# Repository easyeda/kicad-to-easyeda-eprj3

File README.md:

English | [中文](README.zh-CN.md)

# kicad-to-easyeda-eprj3

Convert KiCAD project files to the eprj3 project format of EasyEDA Pro, and KiCad libraries to the EasyEDA Pro library format `.elibz2`.

## Features

- **Project conversion**: Batch-traverses all `.kicad_sch` / `.kicad_pcb` files under a directory and generates a complete eprj3 folder project (`<name>.eprj3` index + `sch/` + `pcb/`)
- **Library conversion**: Packs all KiCad libraries under a directory (`*.kicad_sym` symbol libs + `*.pretty/*.kicad_mod` footprint libs) into a single EasyEDA Pro library file `.elibz2`
- **No-install browser version**: `kicad-to-eprj3.html` converts projects entirely in the browser (no Node.js, no upload)
- **Standalone JS**: one file usable both as a Node.js CLI and as a browser script, built by `npm run build`

## Requirements

- Node.js ≥ 18. There are **no npm dependencies** (runtime or development); the browser page needs none either.

## Browser version (no installation)

Download `kicad-to-eprj3-<version>.zip` from the GitHub **Releases** page and unzip it. Open `kicad-to-eprj3.html` in a recent Chrome/Edge:

1. Add one or more KiCad project folders. Clicking a folder scans it and lists the projects inside, so several can be ticked at once; multiple folders can also be dropped together, and the picker can be used repeatedly.
2. Click **Convert** — everything is processed locally; nothing is uploaded.
3. Download the `.eprj3.zip`, unzip it, then open `<project>/<project>.eprj3` in EasyEDA Pro.

Choosing a folder uses the browser's File System Access API, so no “upload files” confirmation appears (Chrome/Edge).

The zip also contains the standalone JS, this guide (bilingual) and the license.

### Online (GitHub Pages)

The page is also published as a single-page site: **https://easyeda.github.io/kicad-to-easyeda-eprj3/**

`.github/workflows/pages.yml` builds `dist/kicad-to-eprj3.html` and deploys it as the Pages `index.html` on every push to `main` (or manually via *Actions → Deploy browser page to GitHub Pages → Run workflow*). In a fork, enable **Settings → Pages → Build and deployment → Source: GitHub Actions** once; the workflow can also try to enable it on the first run.

> If your organization disables GitHub Pages for the repository, the workflow detects it and skips deployment with a notice (no red build). The same single file is also attached to every GitHub Release — download **`kicad-to-eprj3.html`** and open it locally, or host it on any static file server. No build step is needed to use it.

## Usage

### 1) KiCad project → eprj3 project (batch)

```bash
node scripts/convert-kicad.js convert <KiCad project directory> <output directory> [--project-name <name>]
```

Example — convert the sample project shipped with this repository:

```bash
node scripts/convert-kicad.js convert example/kicad/kicad-project ./eprj3 --project-name kicad-project
```

Output:

```text
Created eprj3 project at D:/…/eprj3
  sch: kicad-project.kicad_sch -> D:/…/eprj3/sch/Schematic1/P1.esch2
  pcb: kicad-project.kicad_pcb -> D:/…/eprj3/pcb/PCB1.epcb2
```

The generated project (`<output directory>/kicad-project.eprj3`, containing `sch/` and `pcb/`) can be opened directly in EasyEDA Pro.

- The two directories are passed positionally: 1st is the KiCad project directory, 2nd is the eprj3 output directory
- Each `*.kicad_sch` under the source directory generates one schematic (`Schematic1`, `Schematic2`, …), and each `*.kicad_pcb` generates one board (`PCB1`, `PCB2`, …)

### 2) KiCad library directory → EasyEDA Pro library package (.elibz2)

```bash
node scripts/convert-kicad-lib.js convert <KiCad library directory> <output.elibz2> [--name <LibName>]
```

Example — put symbol and footprint libraries into one directory and pack them together (the scan is non-recursive; `.kicad_sym` files and `.pretty/` directories must be direct children):

```text
mylibs/
├── Device.kicad_sym
├── LED.kicad_sym
├── Resistor_SMD.pretty/
│   ├── R_0805_2012Metric.kicad_mod
│   └── …
└── LED_SMD.pretty/
    └── …
```

```bash
node scripts/convert-kicad-lib.js convert mylibs ./DeviceLED.elibz2 --name DeviceLED
```

Output:

```text
  sym lib: Device.kicad_sym (533 symbols)
  sym lib: LED.kicad_sym (63 symbols)
  footprint lib: LED_SMD.pretty (100 footprints)
  footprint lib: Resistor_SMD.pretty (67 footprints)
Wrote DeviceLED.elibz2: 596 symbols, 167 footprints (636245 bytes)
```

The resulting `DeviceLED.elibz2` can be installed into your local libraries through EasyEDA Pro's library import.

- Scans the directory for all `*.kicad_sym` (symbol libraries) and `*.pretty/` (footprint libraries, reading their `*.kicad_mod` files) and merges everything into **one** `.elibz2`
- `--name` (optional): overrides the package name (defaults to the output file name minus the `.elibz2` suffix)
- A `.elibz2` is a zip archive containing:
  - `device2.json` — device/symbol/footprint index (uuid → metadata); symbols carry `docType:2`, footprints `docType:4`, and every symbol gets an auto-generated device entry
  - `<LibName>.elibu` — a record stream (same format as `.esch2`/`.epcb2`); each symbol/footprint is written as two segments: `DOCHEAD+META` and `DOCHEAD+records`
- When a symbol's `Footprint` property (e.g. `Resistor_SMD:R_0805`) matches a converted footprint name, the device's `Footprint` attribute is automatically linked to that footprint's uuid
- Power symbols (`symbol_type "power"`) get META `docType:18`; footprint docs include the 19-layer table + `ACTIVE_LAYER` + a full `CANVAS` and carry no `PART` record
- Example: `example/easyeda/easyeda-pro-libs.elibz2` is a reference library package exported from EasyEDA Pro

### 3) Standalone bundle (Node CLI + browser page)

Build the distributable artifacts with:

```bash
npm run build
```

This writes to `dist/`:

| File | Purpose |
| --- | --- |
| `kicad-to-eprj3-<version>.js` | Single-file UMD bundle: Node CLI **and** browser API |
| `kicad-to-eprj3.html` | Self-contained conversion page (bundle inlined) |
| `README.md` | Bilingual end-user guide shipped in the zip |
| `kicad-to-eprj3-<version>.zip` | The three files above + `LICENSE` |

The standalone JS works exactly like the multi-file CLI:

```bash
node dist/kicad-to-eprj3-<version>.js convert <KiCad project directory> <output directory>
node dist/kicad-to-eprj3-<version>.js convert-lib <KiCad library directory> <output.elibz2>
```

In a browser it exposes `window.KicadToEpj3` (`convertProjectFiles`, `zipProject`, `zipStore`, …).

**Versioning / release**: the build workflow (`.github/workflows/build-release.yml`, manual `workflow_dispatch`) bumps the version (default: **patch / last digit**), runs the tests, builds the artifacts, commits the bump to `main`, tags `v<version>` and attaches the zip to the GitHub release. Every update must bump the last digit (`node build/version.js patch`, or `npm run version:bump`). The workflow needs permission to push to `main` (allow GitHub Actions in the branch protection rules if the push is rejected).

## Conversion Coverage (best-effort)

Output strictly follows the official format documentation from [easyeda-format-skill](https://github.com/easyeda/easyeda-format-skill) (types / field definitions / JSON Schemas), calibrated against real exported data where the schemas diverge from actual app output; see also the [official eprj3 format example project](https://github.com/easyeda/easyeda-eprj3-format):

| KiCad | eprj3 |
| --- | --- |
| `lib_symbols` (schematic-embedded symbol libs) | Embedded `SYMBOL` doc segments (`PART`/graphics/pins) + `DEVICE` doc segments in `.esch2` |
| `symbol` instances (with `property`, `mirror`) | `COMPONENT` (`partId` → embedded `PART`, `DeviceName` → `DEVICE`, mirror/rotation converted) + `Designator`/`Value` `ATTR` |
| `wire` | `WIRE` + multiple `LINE` records sharing a `lineGroup` |
| `bus` / `bus_entry` | `BUS` + `LINE` / `BUSENTRY` |
| `junction` | Wire split/grouping point only (same `lineGroup`); no dot is drawn |
| `no_connect` | Two `LINE` records (X marker) |
| `label` / `global_label` / `hierarchical_label` | `NET` attr on the wire group / net flag / net port |
| `text` / `text_box` | `TEXT` (+ `RECT` border) |
| `polyline` / `rectangle` / `circle` / `arc` / `bezier` | `POLY` / `RECT` / `CIRCLE` / `ARC` (center from three points) / `BEZIER`, with stroke/fill styles mapped |
| `image` | `OBJ` (base64-embedded) |
| `sheet` (hierarchy) | Reuse block symbol (`SYMBOL` docType 17) + `COMPONENT`, linked to its own child schematic (CBB instances) |
| `power` symbol / `PWR_FLAG` | Net flag (docType 18) / non-electrical symbol (docType 21, no `PIN`, keeps the KiCad glyph) |
| Pin electrical/graphic types | Numeric `PIN.electric` / `PIN.pinShape` mapping |
| `footprint` (with `pad`) | Embedded `FOOTPRINT` doc segments (`PART`/`PAD`/silkscreen graphics) + `DEVICE` doc segments + `COMPONENT` placements + `Designator`/`Footprint`/`Device` `ATTR` in `.epcb2` |
| pad nets / oval drills | `PAD_NET` (component-pad binding) + `NET` index records / `holeType ROUND` width×height |
| `segment` / `arc` (PCB traces) | `FILL` on the corresponding layer (straight tracks as closed thin polygons; track arcs as closed polygons with `ARC` segments) |
| `via` | `VIA` (net, hole and pad diameters) |
| `zone` | `POUR` (`pourType`/`keepIsland`) + one `POURED` per zone/layer (`pourFill`, head id linked to the `POUR`); keepouts → `REGION` (`regionType PROHIBIT` + `prohibitType`) |
| `dimension` (aligned/orthogonal/radial/leader) | `DIMENSION` (`dimensionType LENGTH-CONSTRAINT` + `controlDot`) |
| `gr_line` / `gr_arc` / `gr_rect` / `gr_poly` / `gr_circle` / `bezier` | `LINE` / `ARC` / closed `POLY` (circles as `["CIRCLE",…]` paths, beziers as `"C"`-segment paths) |
| `gr_text` | `STRING` (alignment origin, mirroring, knockout→reverse) |
| `gr_rect`/`gr_line`/`gr_arc`/`gr_poly` on `Edge.Cuts` | Stitched into `POLY` `BOARD_OUTLINE` (`layerId=11`) |
| Layer mapping | `F.Cu=1`, `B.Cu=2`, `F.SilkS=3`, `B.SilkS=4`, `F.Mask=5`, `Edge.Cuts=11`, `In{n}.Cu=14+n`…; the PCB doc carries the official 60-layer table and enables the inner layers the KiCad stack actually uses (`use/show`), so their tracks and pours are not dropped |

- Unit conversion: KiCad mm → eprj3 mil (×39.3700787); axis flip: KiCad Y-down → eprj3 Y-up; rotation (360−deg)%360
- FOOTPRINT documents for bottom-side components are stored top-canonical (F/B copper/silk layers swapped, footprint-local Y mirrored); the client mirrors the document when placing the COMPONENT, so pads land on the correct side and asymmetric pad coordinates are not permuted
- uuid linkage (official convention): the `DOCHEAD.uuid` of the `.esch2` page / `.epcb2` / `.ecfg` equals the `sheets` / `pcbs` / `schematics` uuid in the index respectively
- Also generates `sch/<name>/<name>.ecfg` (design-rules skeleton) and `.evar` (assembly variants, empty)
- **Not migrated**: 3D models, net classes, SPICE models, custom rules; elements that cannot be translated are skipped with a warning

### Library Conversion Coverage (.elibz2)

| KiCad library | .elibz2 |
| --- | --- |
| Every `(symbol …)` in a `*.kicad_sym` | `SYMBOL` doc segment (`PART`/`PIN`/`POLY`/`RECT`/`CIRCLE`/`ARC`/`BEZIER`) + a `device2.json` symbol index entry + a device entry |
| `symbol_type "power"` | META `docType:18` (power class) |
| Symbol `property` entries (other than Reference/Value) | Passed through into device `attributes` |
| Symbol `Footprint` property | Auto-written to the device's `attributes.Footprint` (uuid) when it matches a footprint name |
| Every `(footprint …)` in `*.pretty/*.kicad_mod` | `FOOTPRINT` doc segment (19-layer table + `PAD`/`POLY`/`ARC` + `ACTIVE_LAYER`) + a `device2.json` footprint index entry |
| pad `thru_hole`/`oval` drills | `PAD` `holeDiameter`/`holeWidth`/`holeType ROUND` |
| `F.SilkS`/`B.SilkS` graphics | layerId 3/4; Fab/CrtYd/Dwgs and the rest → Document layer 13 |

## Directory Structure

```
kicad-to-easyeda-eprj3/
├── scripts/
│   ├── convert-kicad.js      ← Project CLI wrapper
│   ├── convert-kicad-lib.js  ← Library CLI wrapper
│   ├── browser/
│   │   ├── entry.js          ← Standalone bundle entry (Node CLI + browser API)
│   │   ├── vfs.js            ← In-memory filesystem used by the browser page
│   │   ├── active-fs.js      ← Active filesystem switch for one conversion
│   │   ├── node-fs.js / node-path.js ← Host Node fs/path injected by the bundle
│   │   ├── node-shims/       ← fs/path/crypto/zlib facades for browsers + Node
│   │   └── zip-store.js      ← Dependency-free STORE-mode ZIP writer for downloads
│   └── lib/
│       ├── convert-project.js ← Project conversion flow (shared by CLI + bundle)
│       ├── convert-lib.js    ← Library conversion flow (shared by CLI + bundle)
│       ├── kicad.js          ← KiCad S-expression parser
│       ├── kicad-to-eprj3.js ← Symbols/footprints → eprj3 records
│       ├── schematic-convert.js ← Schematic page conversion (symbols/net flags/net ports/hierarchy/frame)
│       ├── pcb-convert.js    ← PCB conversion (tracks/vias/footprints/pours/stackup/design rules)
│       ├── convert-util.js   ← Shared conversion constants and helpers
│       ├── frame-template.js ← A4 drawing-sheet template instantiation
│       ├── eprj3.js          ← eprj3 read/write core (from easyeda-eprj3-skill, corrected against the official example)
│       ├── elibz2.js         ← .elibz2 package assembly (device2.json + .elibu)
│       ├── zip.js            ← Dependency-free zip read/write (zlib deflate/store)
│       └── utils.js
├── build/
│   ├── bundle.js             ← Builds the standalone JS, HTML page and zip
│   ├── version.js            ← Version bump (patch/minor/major/none)
│   ├── check-licenses.js     ← Enforces MIT/Apache-2.0 for every dependency
│   ├── licenses/             ← MIT license texts shipped in the zip
│   ├── app.html              ← Browser page template
│   └── artifact-readme.md    ← Bilingual end-user guide shipped in the zip
├── .github/workflows/
│   ├── build-release.yml     ← Manual build → version bump → tag → release asset
│   └── pages.yml             ← Push to main → build the single-page site for GitHub Pages
├── example/
│   ├── easyeda/              ← Reference EasyEDA Pro library package easyeda-pro-libs.elibz2
│   └── kicad/                ← Sample KiCad project
└── test/
    ├── smoke.js              ← End-to-end smoke suite (165 assertions)
    ├── bundle.test.js        ← Standalone bundle / browser API / HTML tests (23 assertions)
    ├── ui.test.js            ← Browser page folder-scan / multi-select / modal tests (11 assertions)
    ├── compare/              ← KiCad ↔ eprj3 comparison (netlist/BOM/PCB primitives/stackup/ratlines)
    └── validate-format.js    ← Format validator checking generated records against the official JSON Schemas
```

## Testing

```bash
npm test          # license check + smoke + hostpath + standalone bundle + UI tests
npm run build     # dist/kicad-to-eprj3-<version>.{js,zip} + kicad-to-eprj3.html
```

Generated records can additionally be validated one by one against the official Schemas (`sch`/`pcb`/`lib` contexts; `lib` routes each doc's records by its docType):

```bash
node test/validate-format.js <generated .esch2|.epcb2|.elibu> <sch|pcb|lib>
```

> The validator uses `validate.js` from [easyeda-format-skill](https://github.com/easyeda/easyeda-format-skill), located in the sibling directory (or via the `EASYEDA_FORMAT_SKILL` environment variable) when present; it is not vendored. Note: the official Schemas slightly diverge from real app exports (e.g. `POUR.pourType`, PCB `ATTR.groupID`, the `DIMENSION` structure); the validator is calibrated to the real exported data.

## Related Projects

- [easyeda-format-skill](https://github.com/easyeda/easyeda-format-skill) — The EasyEDA Pro file format skill pack (type index, per-primitive field definitions, JSON Schemas, validate.js); the authoritative format reference for this repository
- [easyeda-eprj3-skill](https://github.com/easyeda/easyeda-eprj3-skill) — A skill pack that teaches AI coding assistants to generate `.eprj3` projects from scratch; `scripts/lib/eprj3.js` and `utils.js` in this repository come from that project's core library
- [easyeda-eprj3-format](https://github.com/easyeda/easyeda-eprj3-format) — Official eprj3 format example project

## License

[Apache-2.0](LICENSE)

Third-party components are all MIT-licensed (the vendored `eprj3.js` / `utils.js` core; full text under `build/licenses/`). The project deliberately avoids npm dependencies — `npm run license:check` (part of `npm test`) enforces that any dependency is MIT or Apache-2.0.

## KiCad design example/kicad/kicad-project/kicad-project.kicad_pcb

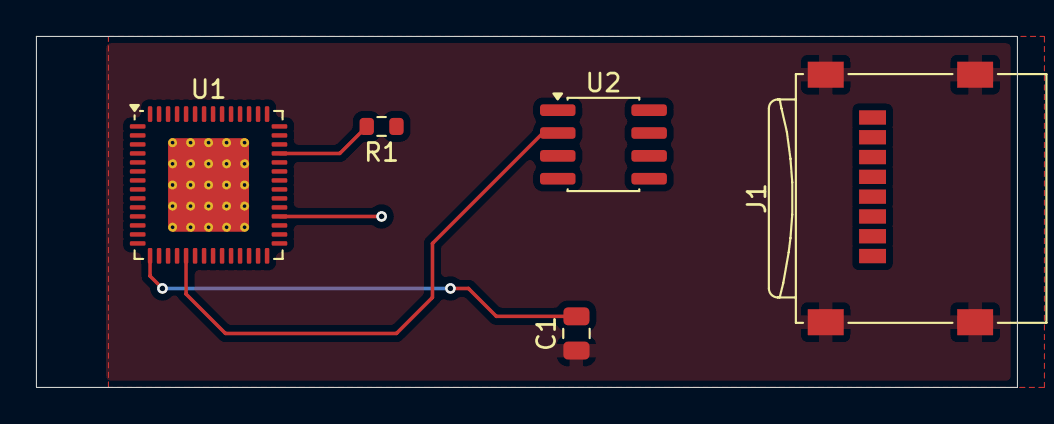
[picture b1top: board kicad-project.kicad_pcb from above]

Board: 2 copper layers, 54.5 x 19.5 mm, 6 parts (1 on the bottom side), 9 nets.

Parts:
C1: C_Small_US; C_0805_2012Metric
J1: Micro_SD_Card; microSD_HC_Wuerth_693072010801
R1: R; R_0603_1608Metric
R2: R_Small_US; R_0805_2012Metric
U1: DSPIC33EV128GM106-E/PT; QFN-56-1EP_8x8mm_P0.5mm_EP4.5x5.2mm_ThermalVias_TopTented
U2: AD8561; SOP-8_3.76x4.96mm_P1.27mm

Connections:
GND: C1.1, J1.SH (SHIELD), R2.2
unnamed: J1.5 (CLK), U1.54 (RP70/RD6)
unnamed: J1.3 (CMD), U1.31 (RPI24/RA8)
unnamed: J1.6 (VSS), U1.53 (RP69/RD5)
unnamed: U1.19 (AVDD), U2.2 (+)
unnamed: R2.1, U1.32 (FLT32/RP36/RB4)
unnamed: R1.2, U1.39 (OSC1/CLKI/AN49/RPI60/RC12)
unnamed: C1.2, U1.15 (PGED3/OA2IN-/AN2/C2IN1-/SS1#/RPI32/CTED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)
unnamed: U1.26 (VDD), U2.3 (-)
